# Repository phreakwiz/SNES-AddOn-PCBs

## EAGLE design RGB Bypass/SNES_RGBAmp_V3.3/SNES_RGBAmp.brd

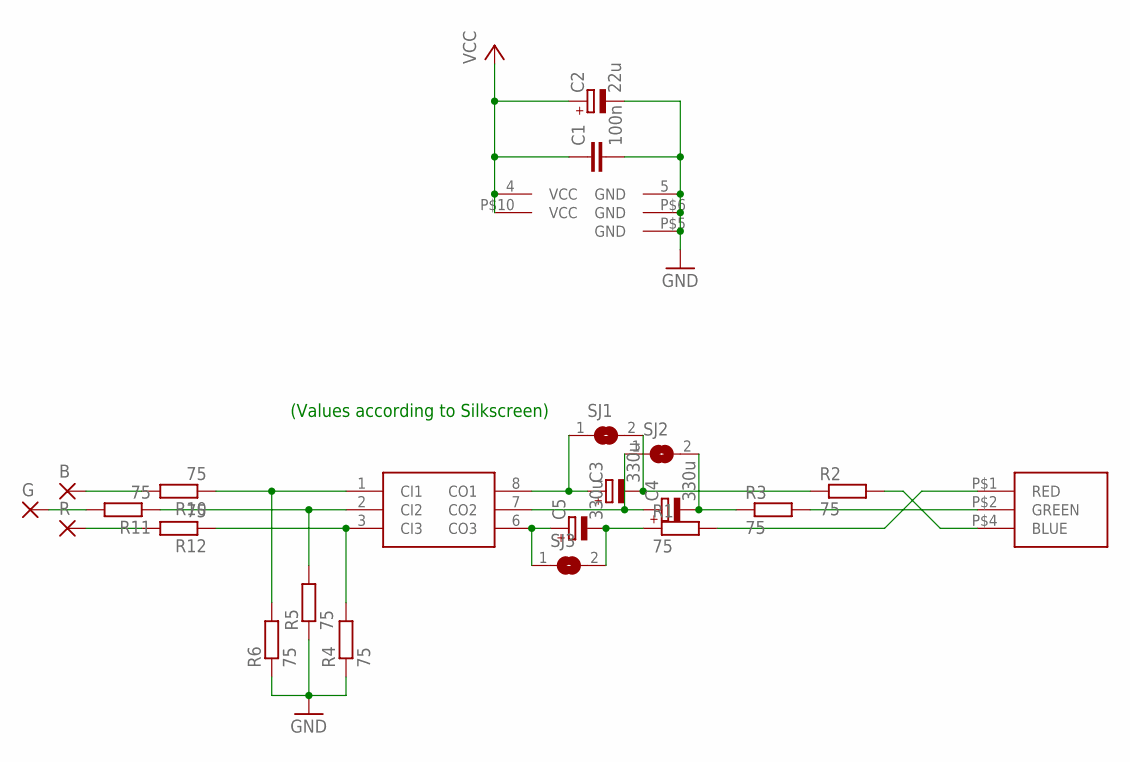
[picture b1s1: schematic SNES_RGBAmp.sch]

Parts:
B: SMD2; SMD1,27-2,54
C1: 100n; Z0805
C2: 22u; SMC_C
C3, C4, C5: 330u; SMC_D
G: SMD2; SMD1,27-2,54
R: SMD2; SMD1,27-2,54
R1, R2, R3, R4, R5, R6, R10, R11, R12: 75; Z0805
SJ1, SJ2, SJ3: SJ
U$1: THS7314
U$2: SNES_MULTIAV_RGB_ONLY

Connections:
GND: C1.2, C2.-, R4.1, R5.1, R6.1, U$1.5 (GND), U$2.P$5 (GND), U$2.P$6 (GND)
unnamed: R6.2, R10.1, U$1.1 (CI1)
unnamed: R5.2, R11.1, U$1.2 (CI2)
unnamed: R4.2, R12.1, U$1.3 (CI3)
unnamed: C3.-, R2.1, SJ1.2
unnamed: R2.2, U$2.P$4 (BLUE)
unnamed: R3.2, U$2.P$2 (GREEN)
unnamed: C4.+, SJ2.1, U$1.7 (CO2)
unnamed: C5.-, R1.1, SJ3.2
unnamed: R1.2, U$2.P$1 (RED)
unnamed: C5.+, SJ3.1, U$1.6 (CO3)
unnamed: C3.+, SJ1.1, U$1.8 (CO1)
unnamed: C4.-, R3.1, SJ2.2
unnamed: B.1, R10.2
unnamed: G.1, R11.2
unnamed: R.1, R12.2
VCC: C1.1, C2.+, U$1.4 (VCC), U$2.P$10 (VCC)

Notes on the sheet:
(Values according to Silkscreen)

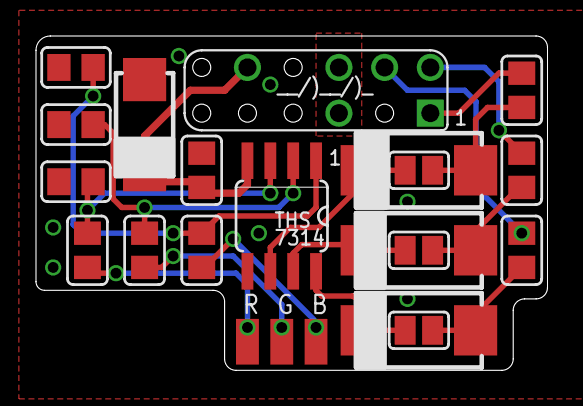
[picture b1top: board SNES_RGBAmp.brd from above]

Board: 2 copper layers, 28.4 x 18.6 mm, 22 parts (0 on the bottom side), 17 nets.
